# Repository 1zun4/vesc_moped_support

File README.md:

# VESC NIU N1S Control

This is my Lisp-based control package for a NIU N1S running a [VESCLabs Maxim+ 150V](https://www.vesclabs.com/product/vl-maxim-plus-150v/). The setup uses both the ESC side (STM) and VESC Express (ESP).

The ECU already handles the light controls on its own. This package adds controls for the ESC inputs.

## Current Status

Supported now:

It is now supported:

- Goes into the no power profile when started or when the sidestand is down.
- Goes into a custom profile set from the GUI when the start button is pressed and the sidestand is up.
- The left mode button selects reverse mode.
- The right mode button selects normal mode.
- The cruise control can be activated by pressing the cruise button and will remain active until it the button is pressed again, braking, lowering the sidestand or reapplying the throttle.

Still planned:

- NIU N1S display support over a TTL to RS485 adapter

## NIU Link hardware design

The [30S NIU Link design draft](hardware/niu_link/README.md) defines a combined
N1S RS485 / NQiX CAN gateway with VESC Express WiFi/cellular connectivity and
integrated auxiliary power conversion. It includes an audit of the legacy KiCad
board, connector extraction, power calculations and verification requirements.
It is not yet a fabrication-ready PCB or verified NQiX implementation.

## Wiring Photo

Wiring photo placeholder: I will add the NIU N1S ESC plug to VESCLabs Maxim+ 150V wiring picture soon.

## ADC App Configuration

- Buttons: Enable Cruise

## Reference

Based on the example package: https://github.com/vedderb/vesc_pkg/tree/main/vl_bike_39p

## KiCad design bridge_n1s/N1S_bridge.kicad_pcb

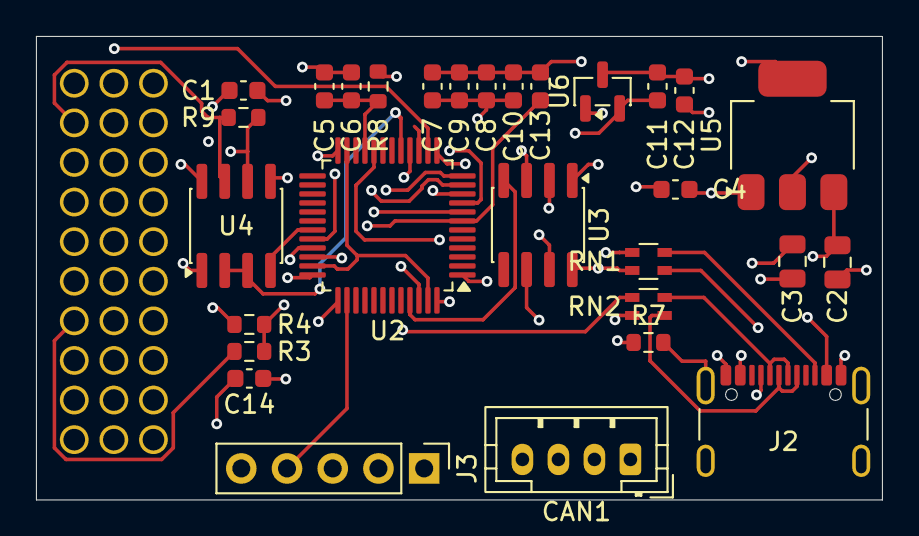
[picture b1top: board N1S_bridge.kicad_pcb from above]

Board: 4 copper layers, 47.0 x 25.8 mm, 30 parts (0 on the bottom side), 36 nets.

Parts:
C1, C4, C11: 100nF; C_0603_1608Metric
C2, C3: 10µF; C_0805_2012Metric
C5, C12: 1µF; C_0603_1608Metric
C6: 10nF; C_0603_1608Metric
C7, C8, C9, C10, C13, C14: 100 nF; C_0603_1608Metric
CAN1: Conn_01x04_Socket; JST_PH_B4B-PH-K_1x04_P2.00mm_Vertical
J1: Conn_01x30; XS-30P
J2: USB_C_Receptacle_USB2.0_16P; USB_C_Receptacle_GCT_USB4105-xx-A_16P_TopMnt_Horizontal
J3: Conn_01x05; PinHeader_1x05_P2.54mm_Vertical
R3: 33kΩ; R_0603_1608Metric
R4: 68kΩ; R_0603_1608Metric
R7: 1MΩ; R_0603_1608Metric
R8: 10 Ω; R_0603_1608Metric
R9: 120 Ω; R_0603_1608Metric
RN1: 5.1k; R_Array_Convex_2x0603
RN2: 22Ω; R_Array_Convex_2x0603
U2: STM32G431C8Tx; LQFP-48_7x7mm_P0.5mm
U3: SN65HVD230; SOIC-8_3.9x4.9mm_P1.27mm
U4: SP3485CN; SOIC-8_3.9x4.9mm_P1.27mm
U5: AMS1117-3.3; SOT-223-3_TabPin2
U6: REF3033; SOT-23

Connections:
+3V3: C1.1, C3.1, C4.1, C7.1, C8.1, C9.1, C10.1, C12.1, C14.1, J3.1, R8.1, U2.1 (VBAT), U2.24 (VDD), U2.36 (VDD), U2.48 (VDD), U3.3 (VCC), U4.8 (VCC), U5.2 (VO), U6.1 (IN)
+5V: C2.1, CAN1.1, J1.12, U5.3 (VI)
/ACC_LOCK: J1.5, U2.11 (PA3)
/BRAKE_LAMP: J1.6, U2.12 (PA4)
/CANH: CAN1.2, U3.7 (CANH)
/CANL: CAN1.3, U3.6 (CANL)
/CRUISE: J1.18, U2.15 (PA7)
/EABS: J1.7, U2.13 (PA5)
/FDCAN1_RX: U2.45 (PB8), U3.4 (R)
/FDCAN1_TX: U2.46 (PB9), U3.1 (D)
/MODE1: J1.1, U2.8 (PA0)
/MODE2: J1.2, U2.9 (PA1)
/MODE3: J1.3, U2.10 (PA2)
/NRST: C13.1, J3.5, U2.7 (PG10)
/RS485_A: J1.10, R9.1, U4.6 (A)
/RS485_B: J1.22, R9.2, U4.7 (B)
/RS485_DE: U2.17 (PB1), U4.2 (~RE), U4.3 (DE)
/SIDE_STAND: J1.11, U2.14 (PA6)
/SWCLK: J3.4, U2.38 (PA14)
/SWDIO: J3.2, U2.37 (PA13)
/THROTTLE: R3.1, R4.1, U2.16 (PB0)
/USART1_RX: U2.32 (PA10), U4.1 (RO)
/USART1_TX: U2.31 (PA9), U4.4 (DI)
/USB_DM: J2.A7 (D-), J2.B7 (D-), RN2.4 (R1.2)
/USB_DP: J2.A6 (D+), J2.B6 (D+), RN2.3 (R2.2)
/VDDA: C5.1, C6.1, R8.2, U2.21 (VDDA)
/VREF+: C11.1, U2.20 (VREF+), U6.2 (OUT)
GND: C1.2, C2.2, C3.2, C4.2, C5.2, C6.2, C7.2, C8.2, C9.2, C10.2, C11.2, C12.2, C13.2, C14.2, CAN1.4, J1.4, J1.13, J1.15, J1.24, J2.A1 (GND), J2.A12 (GND), J2.B1 (GND), J2.B12 (GND), J3.3, R4.2, R7.2, RN1.1 (R1.1), RN1.2 (R2.1), U3.2 (GND), U3.8 (Rs), U4.5 (GND), U5.1 (GND), U6.3 (GND)
unnamed: J1.27, R3.2
unnamed: J2.A5 (CC1), RN1.3 (R2.2)
unnamed: J2.B5 (CC2), RN1.4 (R1.2)
unnamed: J2.SH (SHIELD), R7.1
unnamed: J2.A4 (VBUS), J2.A9 (VBUS), J2.B4 (VBUS), J2.B9 (VBUS)
unnamed: RN2.1 (R1.1), U2.33 (PA11)
unnamed: RN2.2 (R2.1), U2.34 (PA12)
unnamed: U2.23 (VSS), U2.35 (VSS), U2.47 (VSS)

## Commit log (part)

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2026-05-22 chore: update README
2026-05-22 feat: build workflow
2026-06-28 feat: 12V AUX, ignition, alarm and regen brake
    The 12V AUX is a temporary solution for my own setup which is currently lacking a DC-DC converter to power the original 60V hardware (which usually powers 12V & 5V on it's own).
2026-06-28 feat: power AUX output 2 alongside AUX 1
